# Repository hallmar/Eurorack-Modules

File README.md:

# Eurorack-Modules
Hardware: cc-by-sa-3.0

Software: CC BY-SA 4.0

All of the code in this repository is for Arduino.

But if you want to sell or do something with the software or hardware then it'd be nice to include my name and link to my Github somewhere :)

This is a general repository for any and all eurorack modules that i have designed.
I also put DIY stuff here that I made PCB's from some other designers schematic. For example the MFOS PCB.

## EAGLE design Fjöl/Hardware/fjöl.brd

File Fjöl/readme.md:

# Fjöl 4-Voice Midi synth

Small demo video with non working LED's: https://www.youtube.com/watch?v=nTqA_WNiwQo

Current hardware uses a high quality DAC(PCM5100) with 16bit/44.1kHz quality.

Fjöl is a 
4 voice polyphonic Phase modulation synthesizer. Using only sine waves you can get the same sounds as an FM synthesizer.

* digital ladder LPF with resonance
* usb A host
* 3 operator Phase modulation with 3 algorithms(so far)
* two endless encoders with CV input for adjusting 8 different parameters 
* MIDI IN and MIDI THRU with type A midi minijacks as per MIDI standard.
* optional V/OCT and gate per voice expander also in the works
* i2c compatibility with Monome Teletype and Monome Crow (using Just Friends commands) is also on the roadmap
* possible Monome Grid compatibility on the roadmap

Encoder parameters are:

* stereo spread of voices
* filter resonance
* filter envelope decay
* glide/portamento
* Operator 2 detune
* Operator 3 detune
* Operator 1 feedback (creates saw like wave)
* Operator 2 feedback

Potentiometers are:

* Operator 2 amplitude
* Operator 2 ratio
* Operator 3 amplitude
* Operator 3 ratio
* VCA Attack 
* VCA Release
* LPF frequency
* Filter envelope amplitude

Algorithms so far:

### Algo 1: 

OP2 -> OP1

OP3 -> OP1

### Algo 2:

OP3 -> OP2 -> OP1

### Algo 3:

OP3 -> OP1

OP2 -> OUT

## Where/how to order
It's all a work in progress.
Hopefully I'll have some beta testing units ready before summer 2023 :)

## Designed With

* KiCAD
* Arduino IDE 
* Visual Studio Code
* Audio System Design Tool for Teensy Audio Library

## Versioning
* 1.0 - [Hardware] Original PCB
* 1.0 - [Software] Original software 
## Authors

* **Hallmar Gauti Halldórsson** (hardware and firmware)

## License
Hardware: CC BY-SA 4.0

Software: CC BY-SA 4.0

But if you want to sell or do something with the software or hardware then it'd be nice to include my name and link to my Github somewhere :)

## Acknowledgments

* All of Mutable Instruments designs have been an insparation and a solid reference for both analog and digital circuits.
https://github.com/pichenettes/eurorack

* The whole idea of a 4 voice poly synth was planted in my head after trying MakeSynthsNotWar's String Theory module.
https://makesynthsnotwar.com/modules/stringtheory/

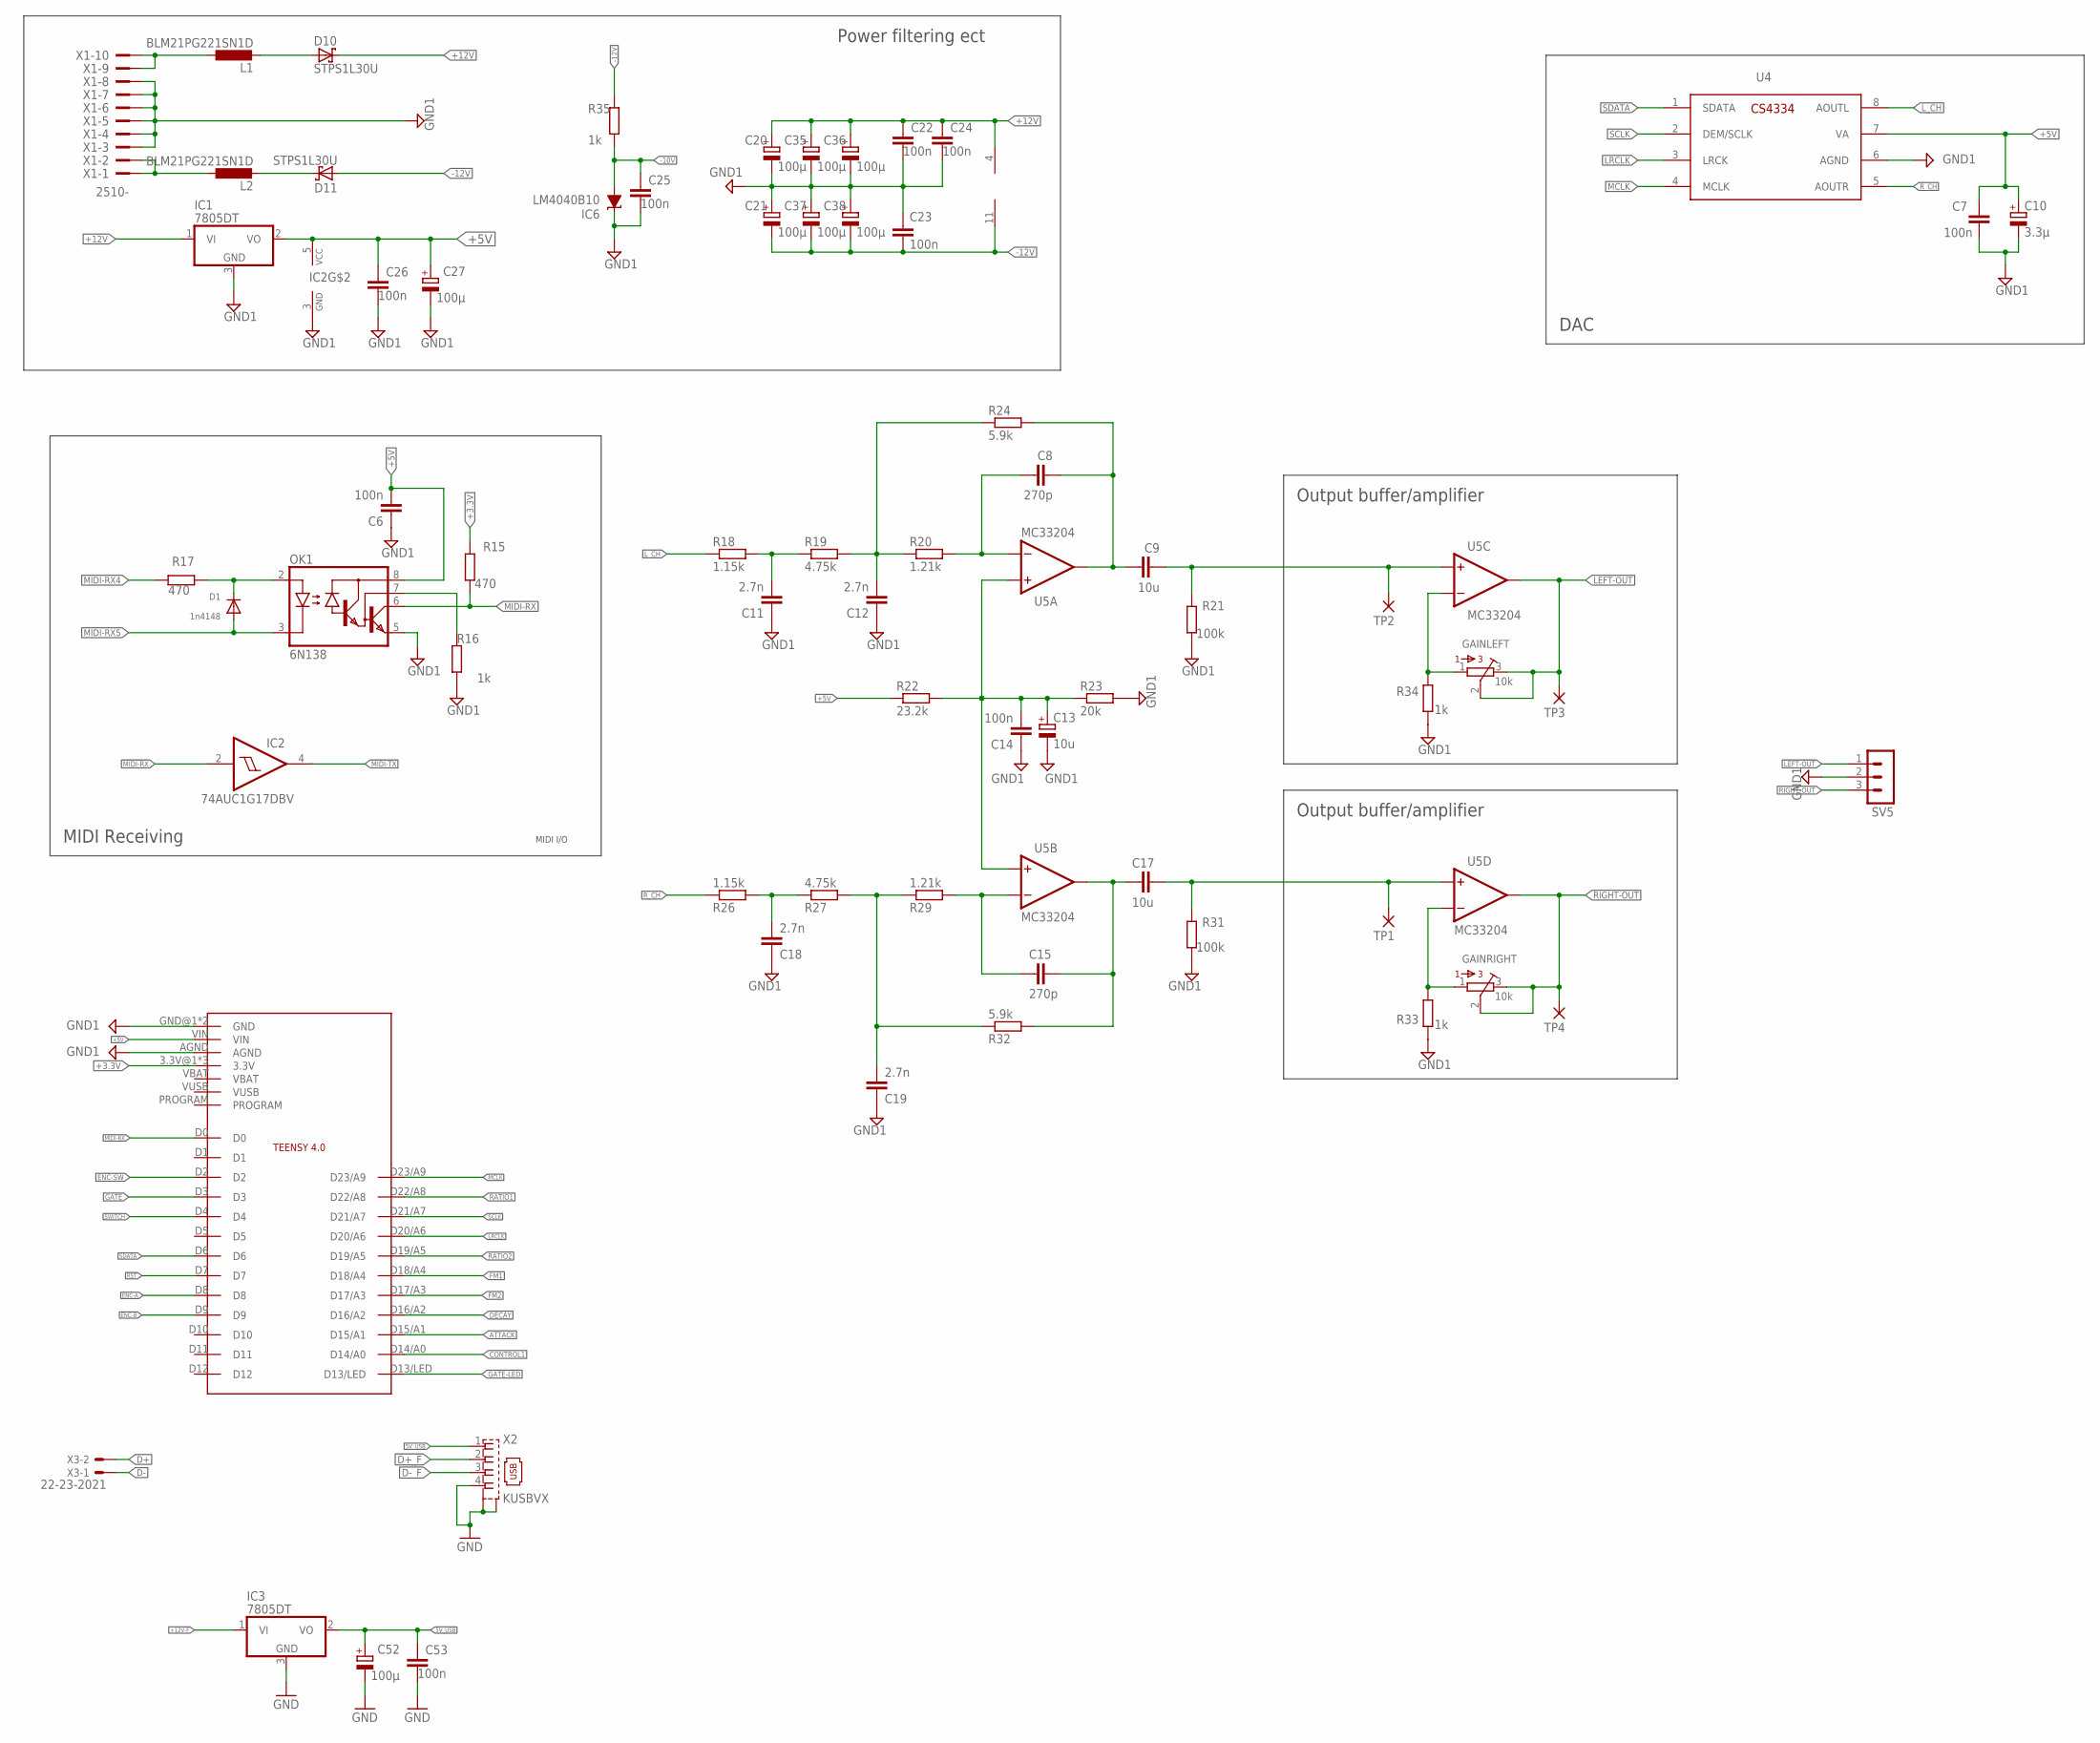
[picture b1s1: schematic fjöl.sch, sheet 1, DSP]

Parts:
C6, C7, C22, C23, C24, C25, C26, C53: 100n; C1206
C8, C15: 270p; C0805
C9, C17: 10u; C1210
C10: 3.3µ; 153CLV-0405
C11, C12, C18, C19: 2.7n; C0805
C13: 10u; 153CLV-0505
C14: 100n; C0805
C20, C21, C27, C35, C36, C37, C38, C52: 100µ; 153CLV-0505
D1: 1n4148; SOD-123
D10, D11: STPS1L30U; SMB
GAINLEFT: 10k; BOURNS_3362P_TRIMMER
GAINRIGHT: 10k; BOURNS_3362P_TRIMMER
IC1, IC3: 7805DT; TO252
IC2: 74AUC1G17DBV; SOT23-5
IC6: LM4040B10; DBZ_R-PDSO-G3
L1, L2: BLM21PG221SN1D; L2012C
OK1: 6N138; DIL08
R15, R17: 470; M1206
R16, R35: 1k; M1206
R18, R26: 1.15k; M0805
R19, R27: 4.75k; M0805
R20, R29: 1.21k; M0805
R21, R31: 100k; M0805
R22: 23.2k; M0805
R23: 20k; M0805
R24, R32: 5.9k; M0805
R33, R34: 1k; M0805
SV5: MA03-1
TP1, TP2, TP3, TP4: 2,54/1,0
U4: CS4334; SOIC127P600X175-8N
U5: MC33204; SO14
U$2: TEENSY4.0
X1: 2510-; PAK100/2500-10
X2: KUSBVX
X3: 22-23-2021

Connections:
5V_USB: C52.+, C53.1, IC3.2 (VO), X2.1
+3.3V: R15.2, U$2.3.3V@1 (3.3V), U$2.3.3V@2 (3.3V), U$2.ON/OFF (3.3V); also elsewhere on the board
+5V: C6.2, C7.1, C10.+, C26.1, C27.+, IC1.2 (VO), IC2.5 (VCC), OK1.8 (VCC), R22.1, U4.7 (VA), U$2.VIN; also elsewhere on the board
+12V: C20.+, C22.1, C24.1, C35.+, C36.+, D10.C, IC1.1 (VI), U5.4 (V+); also elsewhere on the board
+12V-F: IC3.1 (VI); also elsewhere on the board
-10V: C25.1, IC6.2 (A), R35.2; also elsewhere on the board
-12V: C21.-, C23.2, C37.-, C38.-, D11.A, R35.1, U5.11 (V-); also elsewhere on the board
ATTACK: U$2.D15/A1; also elsewhere on the board
CONTROL1: U$2.D14/A0; also elsewhere on the board
D+: X3.2; also elsewhere on the board
D+_F: X2.2; also elsewhere on the board
D-: X3.1; also elsewhere on the board
D-_F: X2.3; also elsewhere on the board
DECAY: U$2.D16/A2; also elsewhere on the board
ENC-A: U$2.D8; also elsewhere on the board
ENC-B: U$2.D9; also elsewhere on the board
ENC-SW: U$2.D2; also elsewhere on the board
FM1: U$2.D18/A4; also elsewhere on the board
FM2: U$2.D17/A3; also elsewhere on the board
GATE: U$2.D3; also elsewhere on the board
GATE-LED: U$2.D13/LED; also elsewhere on the board
GND: C52.-, C53.2, IC3.3 (GND), X2.4, X2.M1 (S1), X2.M2 (S2); also elsewhere on the board
GND1: C6.1, C7.2, C10.-, C11.1, C12.1, C13.-, C14.1, C18.1, C19.1, C20.-, C21.+, C22.2, C23.1, C24.2, C25.2, C26.2, C27.-, C35.-, C36.-, C37.+, C38.+, IC1.3 (GND), IC2.3 (GND), IC6.1 (C), OK1.5 (GND), R16.1, R21.1, R23.2, R31.1, R33.2, R34.2, SV5.2, U4.6 (AGND), U$2.AGND, U$2.GND@1 (GND), U$2.GND@2 (GND), X1.3, X1.4, X1.5, X1.6, X1.7, X1.8; also elsewhere on the board
LEFT: C9.2, R21.2, TP2.1, U5.10 (+IN)
LEFT-OUT: GAINLEFT.2, GAINLEFT.3, SV5.1, TP3.1, U5.8 (OUT); also elsewhere on the board
LRCLK: U4.3 (LRCK), U$2.D20/A6
L_CH: R18.1, U4.8 (AOUTL)
MCLK: U4.4 (MCLK), U$2.D23/A9
MIDI-RX: IC2.2 (I), OK1.6 (VO), R15.1, U$2.D0
MIDI-RX4: R17.2; also elsewhere on the board
MIDI-RX5: D1.A, OK1.3 (C); also elsewhere on the board
MIDI-TX: IC2.4 (O); also elsewhere on the board
unnamed: D1.C, OK1.2 (A), R17.1
unnamed: C11.2, R18.2, R19.1
unnamed: OK1.7 (VB), R16.2
unnamed: C12.2, R19.2, R20.1, R24.1
unnamed: C13.+, C14.2, R22.2, R23.1, U5.3 (+IN), U5.5 (+IN)
unnamed: C8.2, C9.1, R24.2, U5.1 (OUT)
unnamed: C8.1, R20.2, U5.2 (-IN)
unnamed: GAINLEFT.1, R34.1, U5.9 (-IN)
unnamed: C18.2, R26.2, R27.1
unnamed: C19.2, R27.2, R29.1, R32.1
unnamed: C15.1, R29.2, U5.6 (-IN)
unnamed: C15.2, C17.1, R32.2, U5.7 (OUT)
unnamed: GAINRIGHT.1, R33.1, U5.13 (-IN)
unnamed: L1.1, X1.9, X1.10
unnamed: L2.1, X1.1, X1.2
unnamed: D10.A, L1.2
unnamed: D11.C, L2.2
RATIO1: U$2.D22/A8; also elsewhere on the board
RATIO2: U$2.D19/A5; also elsewhere on the board
RIGHT: C17.2, R31.2, TP1.1, U5.12 (+IN)
RIGHT-OUT: GAINRIGHT.2, GAINRIGHT.3, SV5.3, TP4.1, U5.14 (OUT); also elsewhere on the board
RST: U$2.D7; also elsewhere on the board
R_CH: R26.1, U4.5 (AOUTR)
SCLK: U4.2 (DEM/SCLK), U$2.D21/A7; also elsewhere on the board
SDATA: U4.1 (SDATA), U$2.D6; also elsewhere on the board
SWITCH: U$2.D4; also elsewhere on the board

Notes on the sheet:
MIDI I/O
MIDI Receiving
DAC
Output buffer/amplifier
Power filtering ect

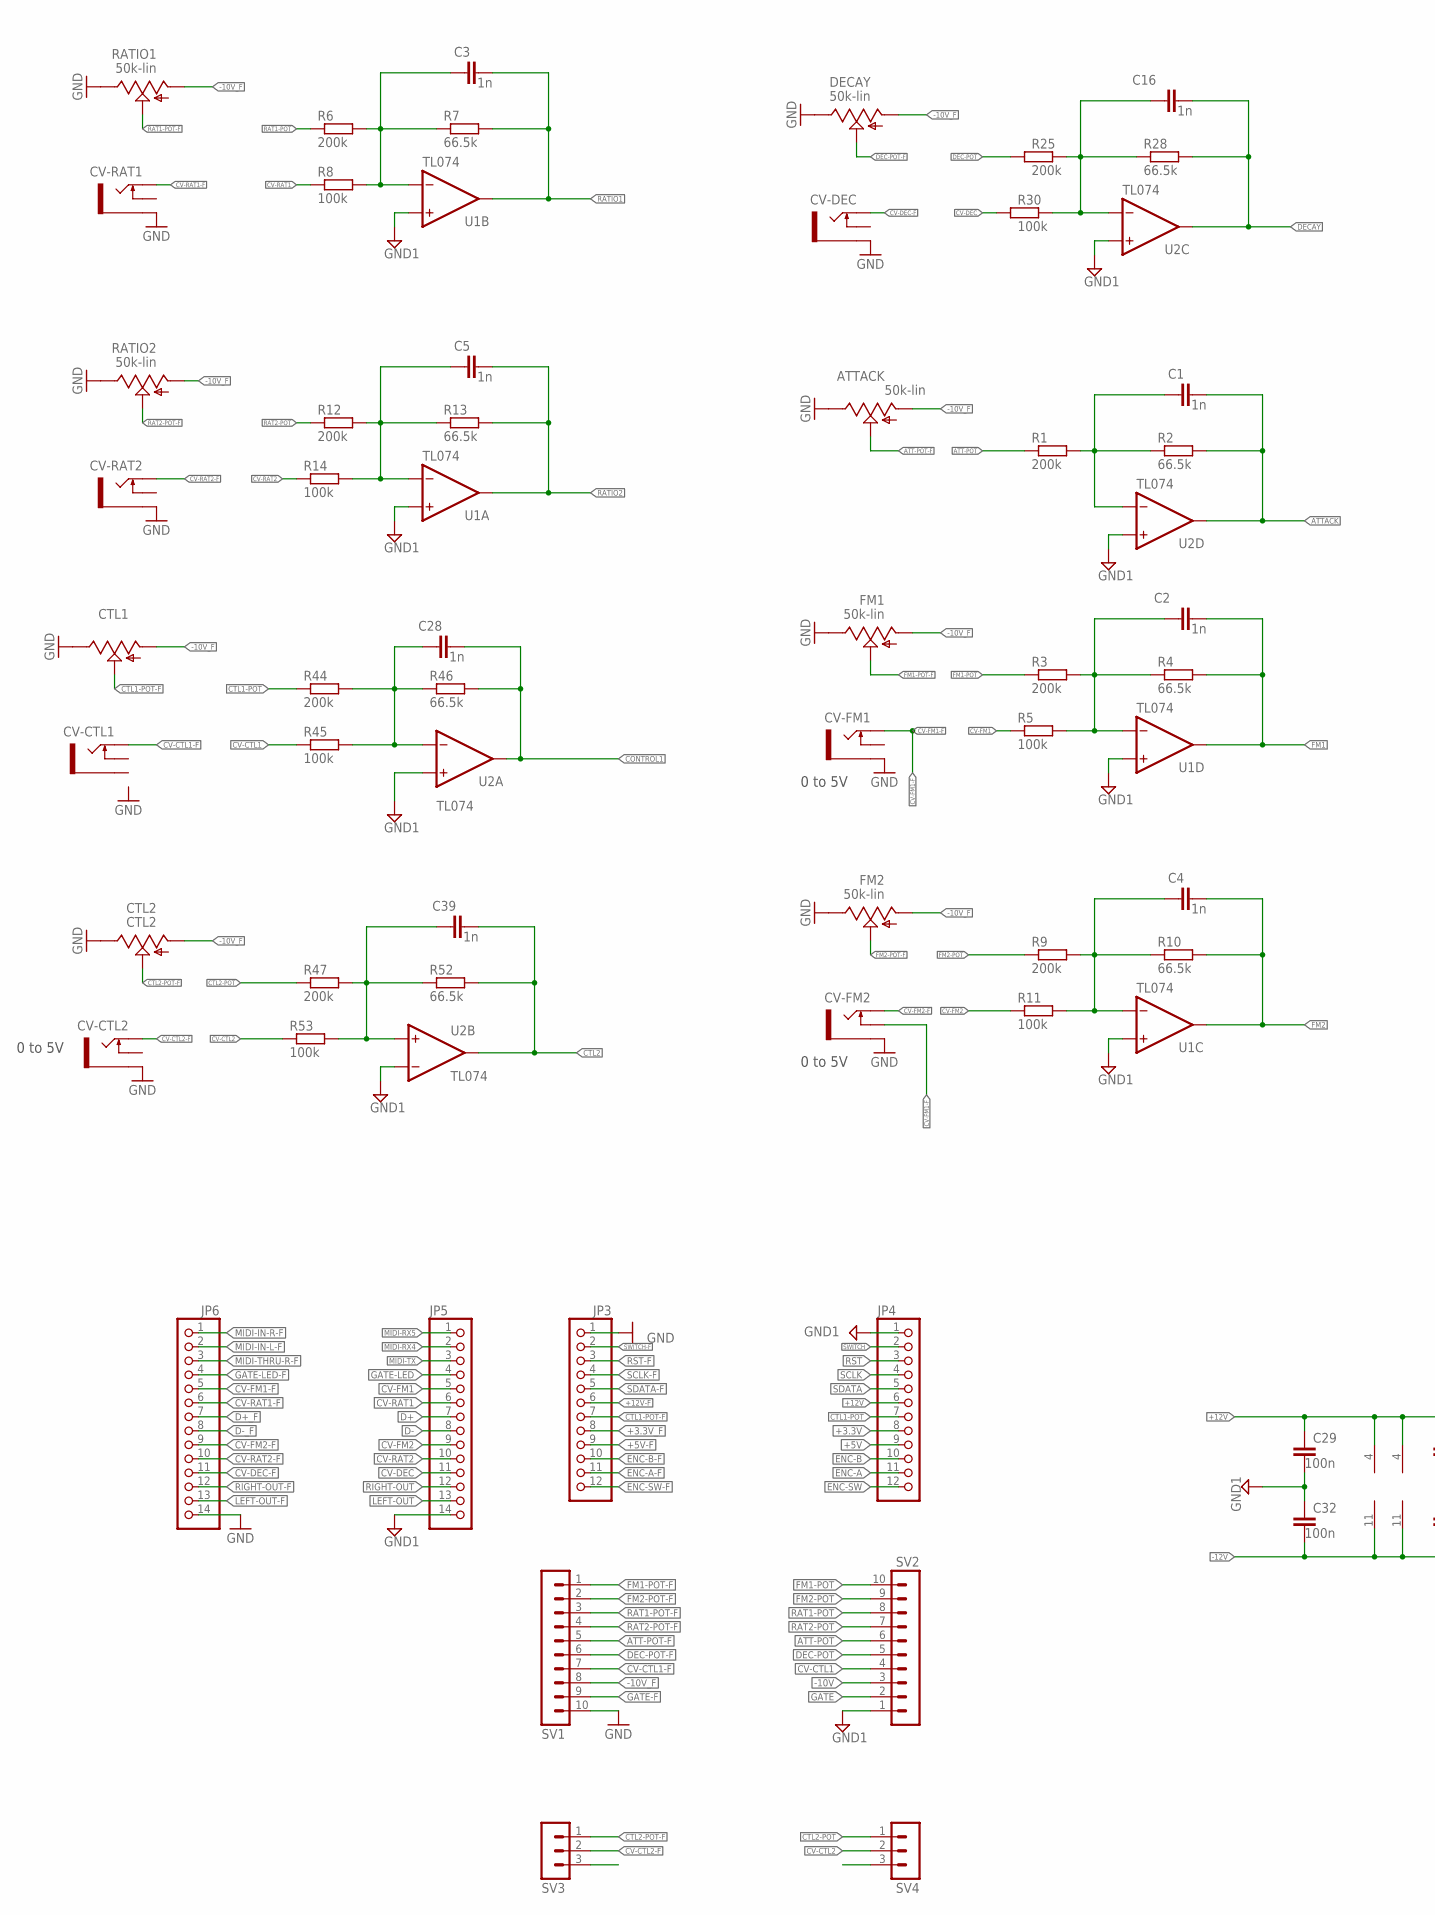
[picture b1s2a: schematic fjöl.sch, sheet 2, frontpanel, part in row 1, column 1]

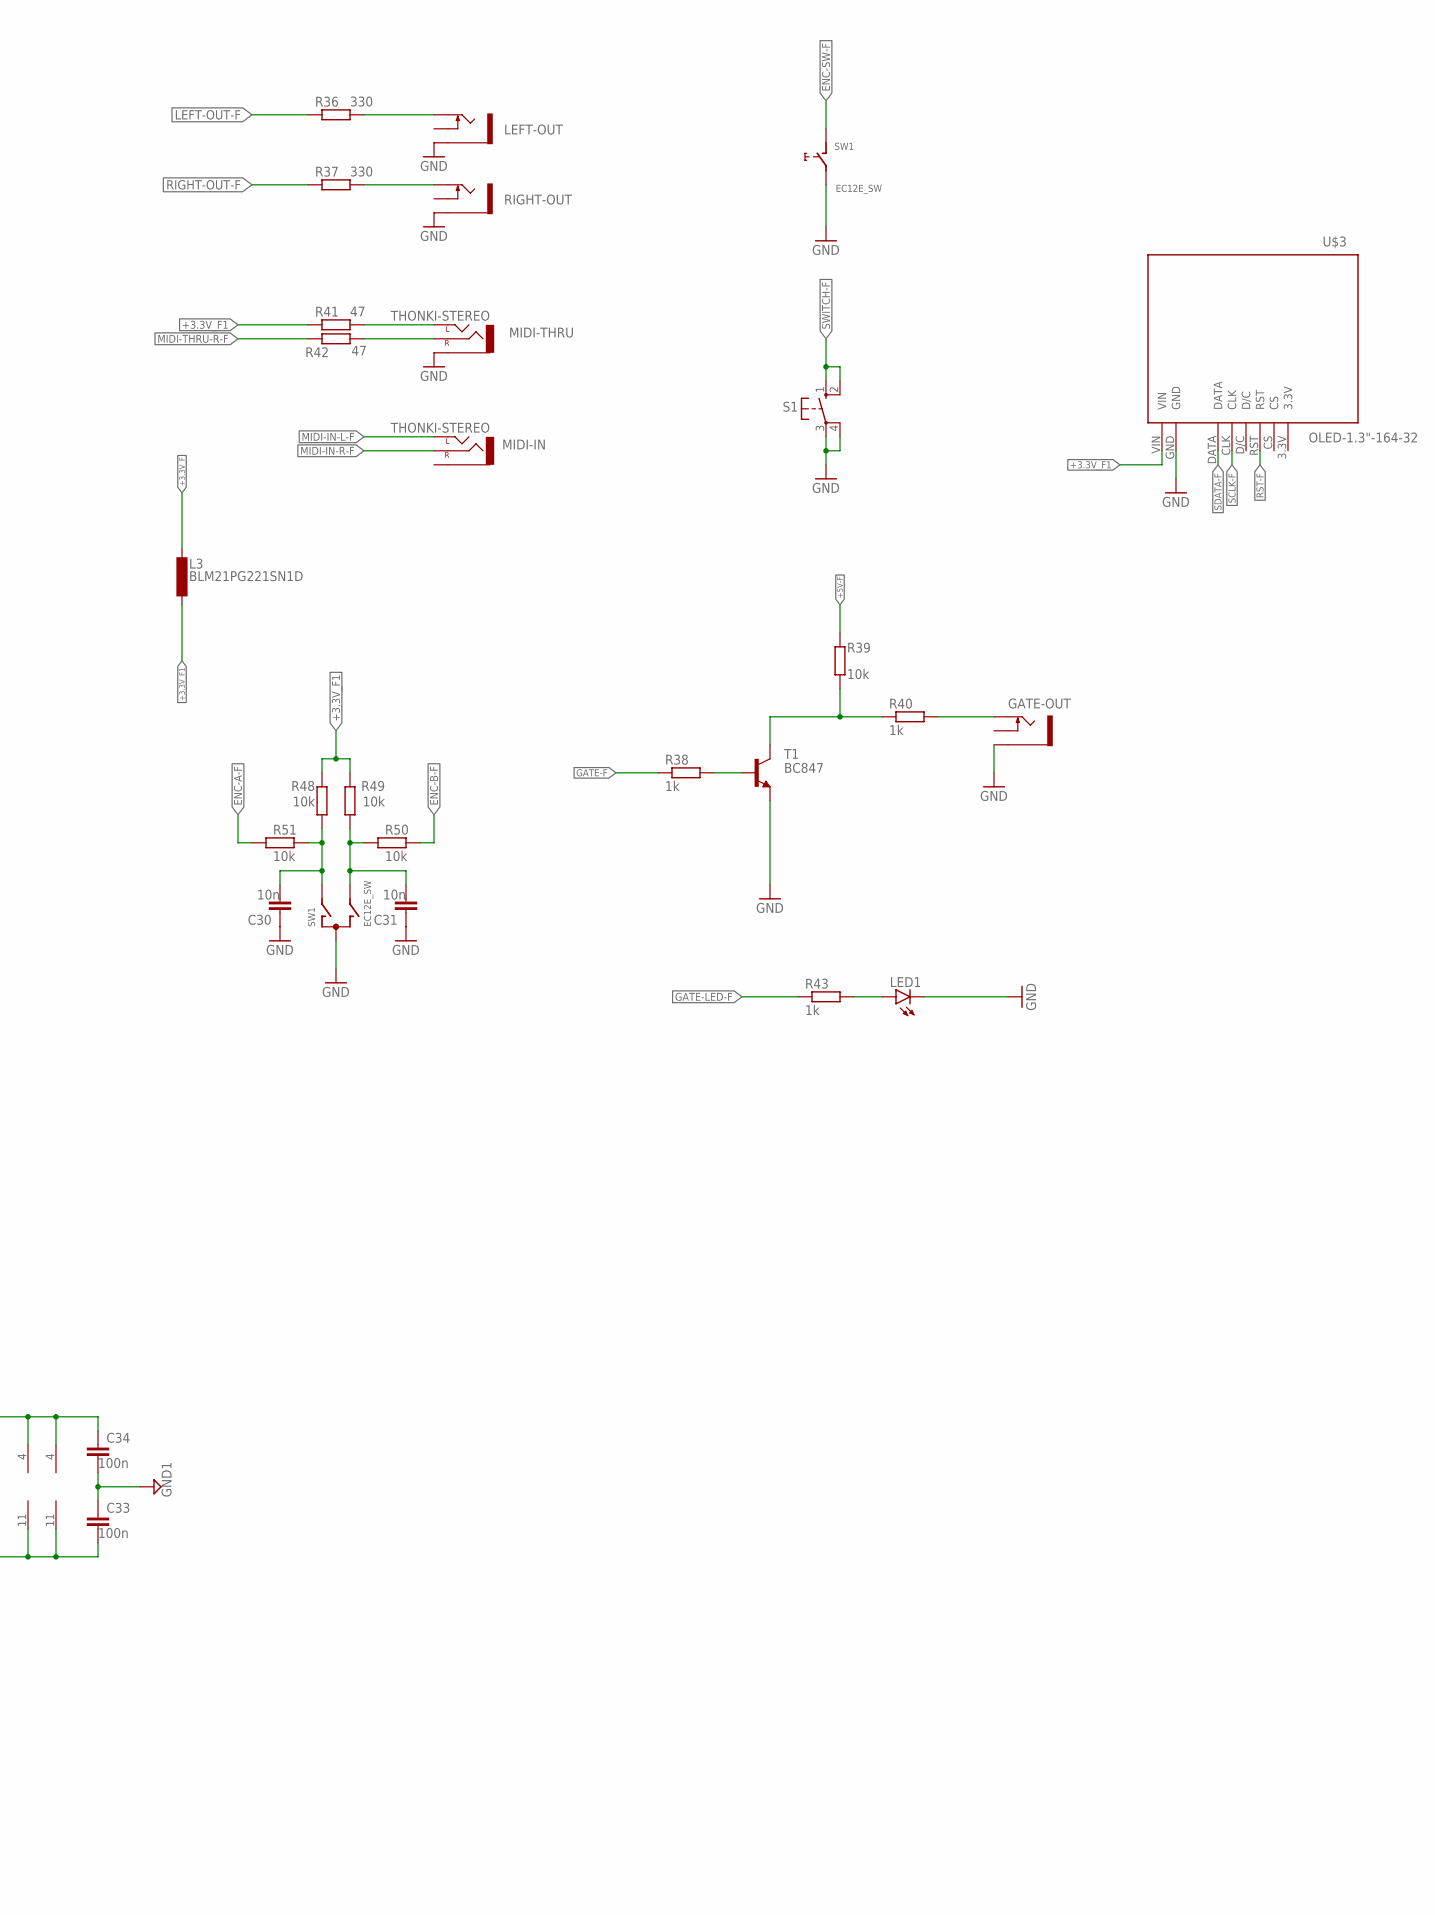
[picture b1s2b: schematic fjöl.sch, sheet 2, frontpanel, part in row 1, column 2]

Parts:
ATTACK: 50k-lin; 9MM_SNAP-IN_POT
C1, C2, C3, C4, C5, C16, C28, C39: 1n; C1206
C29, C32, C33, C34: 100n; C1206
C30, C31: 10n; C1206
CTL1: 9MM_SNAP-IN_POT_; 9MM_SNAP-IN_POT
CTL2: CTL2; 9MM_SNAP-IN_POT
CV-CTL1, CV-CTL2: THONKICONNNEW; WQP-PJ301M-12_JACK
CV-DEC: THONKICONNNEW; WQP-PJ301M-12_JACK
CV-FM1, CV-FM2: THONKICONNNEW; WQP-PJ301M-12_JACK
CV-RAT1, CV-RAT2: THONKICONNNEW; WQP-PJ301M-12_JACK
DECAY: 50k-lin; 9MM_SNAP-IN_POT
FM1, FM2: 50k-lin; 9MM_SNAP-IN_POT
GATE-OUT: THONKICONNNEW; WQP-PJ301M-12_JACK
JP3, JP4: PINHD-1X12; 1X12
JP5, JP6: PINHD-1X14; 1X14
L3: BLM21PG221SN1D; L2012C
LED1: LED3MM
LEFT-OUT: THONKICONNNEW; WQP-PJ301M-12_JACK
MIDI-IN: THONKI-STEREO; WQP-PJ366ST_JACK
MIDI-THRU: THONKI-STEREO; WQP-PJ366ST_JACK
R1, R3, R6, R9, R12, R25, R44, R47: 200k; M1206
R2, R4, R7, R10, R13, R28, R46, R52: 66.5k; M1206
R5, R8, R11, R14, R30, R45, R53: 100k; M1206
R36, R37: 330; M1206
R38, R40, R43: 1k; M1206
R39, R48, R49, R50, R51: 10k; M1206
R41, R42: 47; M1206
RATIO1, RATIO2: 50k-lin; 9MM_SNAP-IN_POT
RIGHT-OUT: THONKICONNNEW; WQP-PJ301M-12_JACK
S1: 10-XX; B3F-10XX
SV1, SV2: MA10-1
SV3, SV4: MA03-1
SW1: EC12E_SW; ALPS_EC12E_SW
T1: BC847; SOT23
U1, U2: TL074; SO14
U$3: OLED-1.3"-164-32

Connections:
+3.3V: JP4.8; also elsewhere on the board
+3.3V_F: JP3.8, L3.2
+3.3V_F1: L3.1, R41.1, R48.2, R49.2, U$3.VIN
+5V: JP4.9; also elsewhere on the board
+5V-F: JP3.9, R39.1
+12V: C29.1, C34.1, JP4.6, U1.4 (V+), U2.4 (V+); also elsewhere on the board
+12V-F: JP3.6; also elsewhere on the board
-10V: SV2.3; also elsewhere on the board
-10V_F: ATTACK.1 (A), CTL1.1 (A), CTL2.1 (A), DECAY.1 (A), FM1.1 (A), FM2.1 (A), RATIO1.1 (A), RATIO2.1 (A), SV1.8
-12V: C32.2, C33.2, U1.11 (V-), U2.11 (V-); also elsewhere on the board
ATT-POT: R1.1, SV2.6
ATT-POT-F: ATTACK.2 (S), SV1.5
ATTACK: C1.2, R2.2, U2.14 (OUT); also elsewhere on the board
B: R38.2, T1.1 (B)
CONTROL1: C28.2, R46.2, U2.1 (OUT); also elsewhere on the board
CTL1-POT: JP4.7, R44.1
CTL1-POT-F: CTL1.2 (S), JP3.7
CTL2: C39.2, R52.2, U2.7 (OUT)
CTL2-POT: R47.1, SV4.1
CTL2-POT-F: CTL2.2 (S), SV3.1
CV-CTL1: R45.1, SV2.4
CV-CTL1-F: CV-CTL1.P$1_TIP (TIP), SV1.7
CV-CTL2: R53.1, SV4.2
CV-CTL2-F: CV-CTL2.P$1_TIP (TIP), SV3.2
CV-DEC: JP5.11, R30.1
CV-DEC-F: CV-DEC.P$1_TIP (TIP), JP6.11
CV-FM1: JP5.5, R5.1
CV-FM1-F: CV-FM1.P$1_TIP (TIP), CV-FM2.P$2_SWITCH (SWITCH), JP6.5
CV-FM2: JP5.9, R11.1
CV-FM2-F: CV-FM2.P$1_TIP (TIP), JP6.9
CV-RAT1: JP5.6, R8.1
CV-RAT1-F: CV-RAT1.P$1_TIP (TIP), JP6.6
CV-RAT2: JP5.10, R14.1
CV-RAT2-F: CV-RAT2.P$1_TIP (TIP), JP6.10
D+: JP5.7; also elsewhere on the board
D+_F: JP6.7; also elsewhere on the board
D-: JP5.8; also elsewhere on the board
D-_F: JP6.8; also elsewhere on the board
DEC-POT: R25.1, SV2.5
DEC-POT-F: DECAY.2 (S), SV1.6
DECAY: C16.2, R28.2, U2.8 (OUT); also elsewhere on the board
ENC-A: JP4.11; also elsewhere on the board
ENC-A-F: JP3.11, R51.2
ENC-B: JP4.10; also elsewhere on the board
ENC-B-F: JP3.10, R50.1
ENC-SW: JP4.12; also elsewhere on the board
ENC-SW-F: JP3.12, SW1.D (1)
FM1: C2.2, R4.2, U1.14 (OUT); also elsewhere on the board
FM1-POT: R3.1, SV2.10
FM1-POT-F: FM1.2 (S), SV1.1
FM2: C4.2, R10.2, U1.8 (OUT); also elsewhere on the board
FM2-POT: R9.1, SV2.9
FM2-POT-F: FM2.2 (S), SV1.2
GATE: SV2.2; also elsewhere on the board
GATE-F: R38.1, SV1.9
GATE-LED: JP5.4; also elsewhere on the board
GATE-LED-F: JP6.4, R43.1
GND: ATTACK.3 (E), C30.1, C31.1, CTL1.3 (E), CTL2.3 (E), CV-CTL2.P$3_SLEEVE (SLEEVE), CV-DEC.P$3_SLEEVE (SLEEVE), CV-FM1.P$3_SLEEVE (SLEEVE), CV-FM2.P$3_SLEEVE (SLEEVE), CV-RAT1.P$3_SLEEVE (SLEEVE), CV-RAT2.P$3_SLEEVE (SLEEVE), DECAY.3 (E), FM1.3 (E), FM2.3 (E), GATE-OUT.P$3_SLEEVE (SLEEVE), JP3.1, JP6.14, LED1.K (C), LEFT-OUT.P$3_SLEEVE (SLEEVE), MIDI-THRU.P$3_SLEEVE (SLEEVE), RATIO1.3 (E), RATIO2.3 (E), RIGHT-OUT.P$3_SLEEVE (SLEEVE), S1.3, S1.4 (P1), SV1.10, SW1.C, SW1.E (2), T1.2 (E), U$3.GND; also elsewhere on the board
GND1: C29.2, C32.1, C33.1, C34.2, JP4.1, JP5.14, SV2.1, U1.3 (+IN), U1.5 (+IN), U1.10 (+IN), U1.12 (+IN), U2.3 (+IN), U2.6 (-IN), U2.10 (+IN), U2.12 (+IN); also elsewhere on the board
LEFT-OUT: JP5.13; also elsewhere on the board
LEFT-OUT-F: JP6.13, R36.1
MIDI-IN-L-F: JP6.2, MIDI-IN.P$1_TIP (LEFT)
MIDI-IN-R-F: JP6.1, MIDI-IN.P$2_SWITCH (RIGHT)
MIDI-RX4: JP5.2; also elsewhere on the board
MIDI-RX5: JP5.1; also elsewhere on the board
MIDI-THRU-R-F: JP6.3, R42.1
MIDI-TX: JP5.3; also elsewhere on the board
unnamed: C1.1, R1.2, R2.1, U2.13 (-IN)
unnamed: C2.1, R3.2, R4.1, R5.2, U1.13 (-IN)
unnamed: C3.1, R6.2, R7.1, R8.2, U1.6 (-IN)
unnamed: C4.1, R9.2, R10.1, R11.2, U1.9 (-IN)
unnamed: C5.1, R12.2, R13.1, R14.2, U1.2 (-IN)
unnamed: LEFT-OUT.P$1_TIP (TIP), R36.2
unnamed: R37.2, RIGHT-OUT.P$1_TIP (TIP)
unnamed: R39.2, R40.1, T1.3 (C)
unnamed: GATE-OUT.P$1_TIP (TIP), R40.2
unnamed: C16.1, R25.2, R28.1, R30.2, U2.9 (-IN)
unnamed: MIDI-THRU.P$1_TIP (LEFT), R41.2
unnamed: MIDI-THRU.P$2_SWITCH (RIGHT), R42.2
unnamed: C39.1, R47.2, R52.1, R53.2, U2.5 (+IN)
unnamed: LED1.A, R43.2
unnamed: C31.2, R49.1, R50.2, SW1.B
unnamed: C30.2, R48.1, R51.1, SW1.A
unnamed: C28.1, R44.2, R45.2, R46.1, U2.2 (-IN)
RAT1-POT: R6.1, SV2.8
RAT1-POT-F: RATIO1.2 (S), SV1.3
RAT2-POT: R12.1, SV2.7
RAT2-POT-F: RATIO2.2 (S), SV1.4
RATIO1: C3.2, R7.2, U1.7 (OUT); also elsewhere on the board
RATIO2: C5.2, R13.2, U1.1 (OUT); also elsewhere on the board
RIGHT-OUT: JP5.12; also elsewhere on the board
RIGHT-OUT-F: JP6.12, R37.1
RST: JP4.3; also elsewhere on the board
RST-F: JP3.3, U$3.RST
SCLK: JP4.4; also elsewhere on the board
SCLK-F: JP3.4, U$3.CLK
SDATA: JP4.5; also elsewhere on the board
SDATA-F: JP3.5, U$3.DATA
SWITCH: JP4.2; also elsewhere on the board
SWITCH-F: JP3.2, S1.1 (S), S1.2 (S1)

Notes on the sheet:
0 to 5V

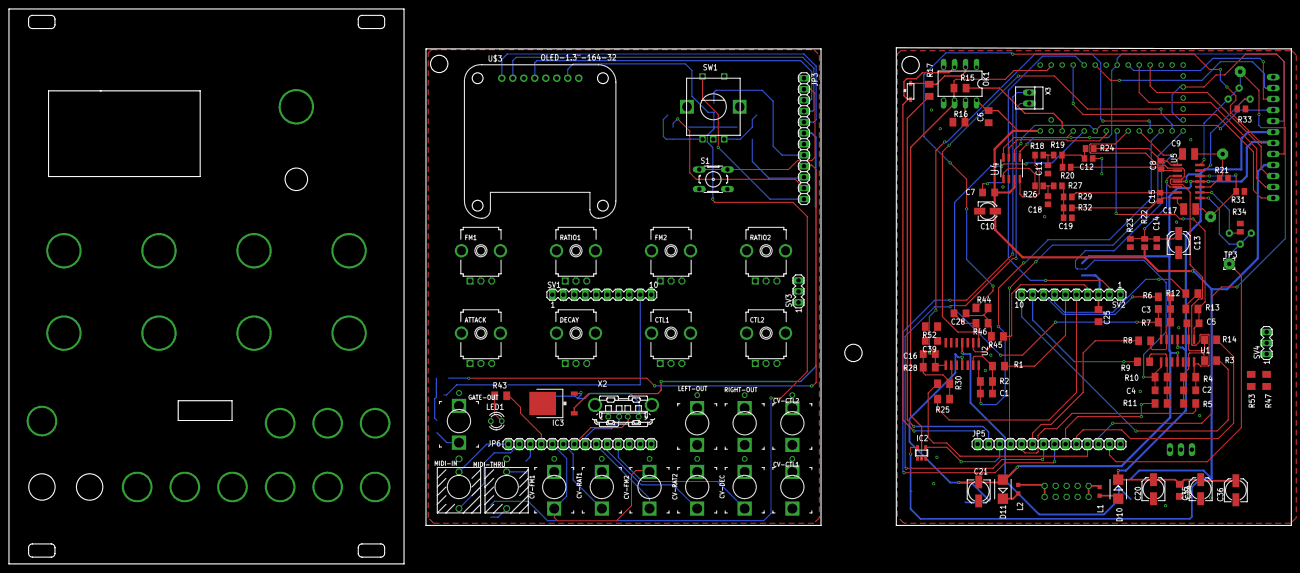
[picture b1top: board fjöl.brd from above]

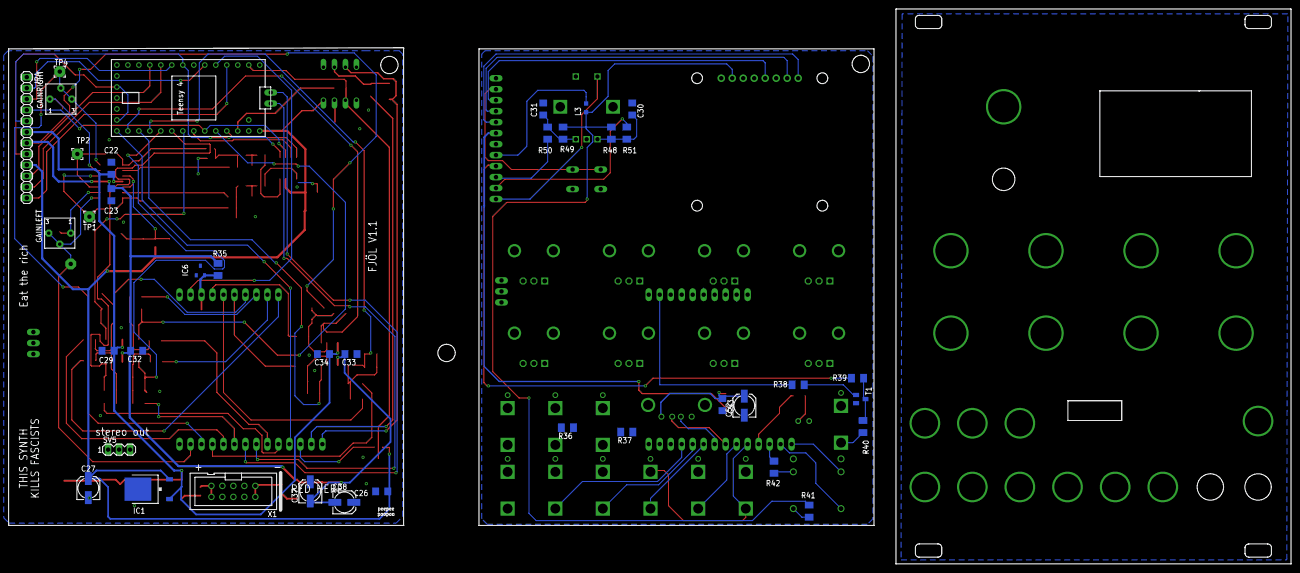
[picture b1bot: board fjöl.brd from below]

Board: 2 copper layers, 296.3 x 128.3 mm, 153 parts (39 on the bottom side), 125 nets.
